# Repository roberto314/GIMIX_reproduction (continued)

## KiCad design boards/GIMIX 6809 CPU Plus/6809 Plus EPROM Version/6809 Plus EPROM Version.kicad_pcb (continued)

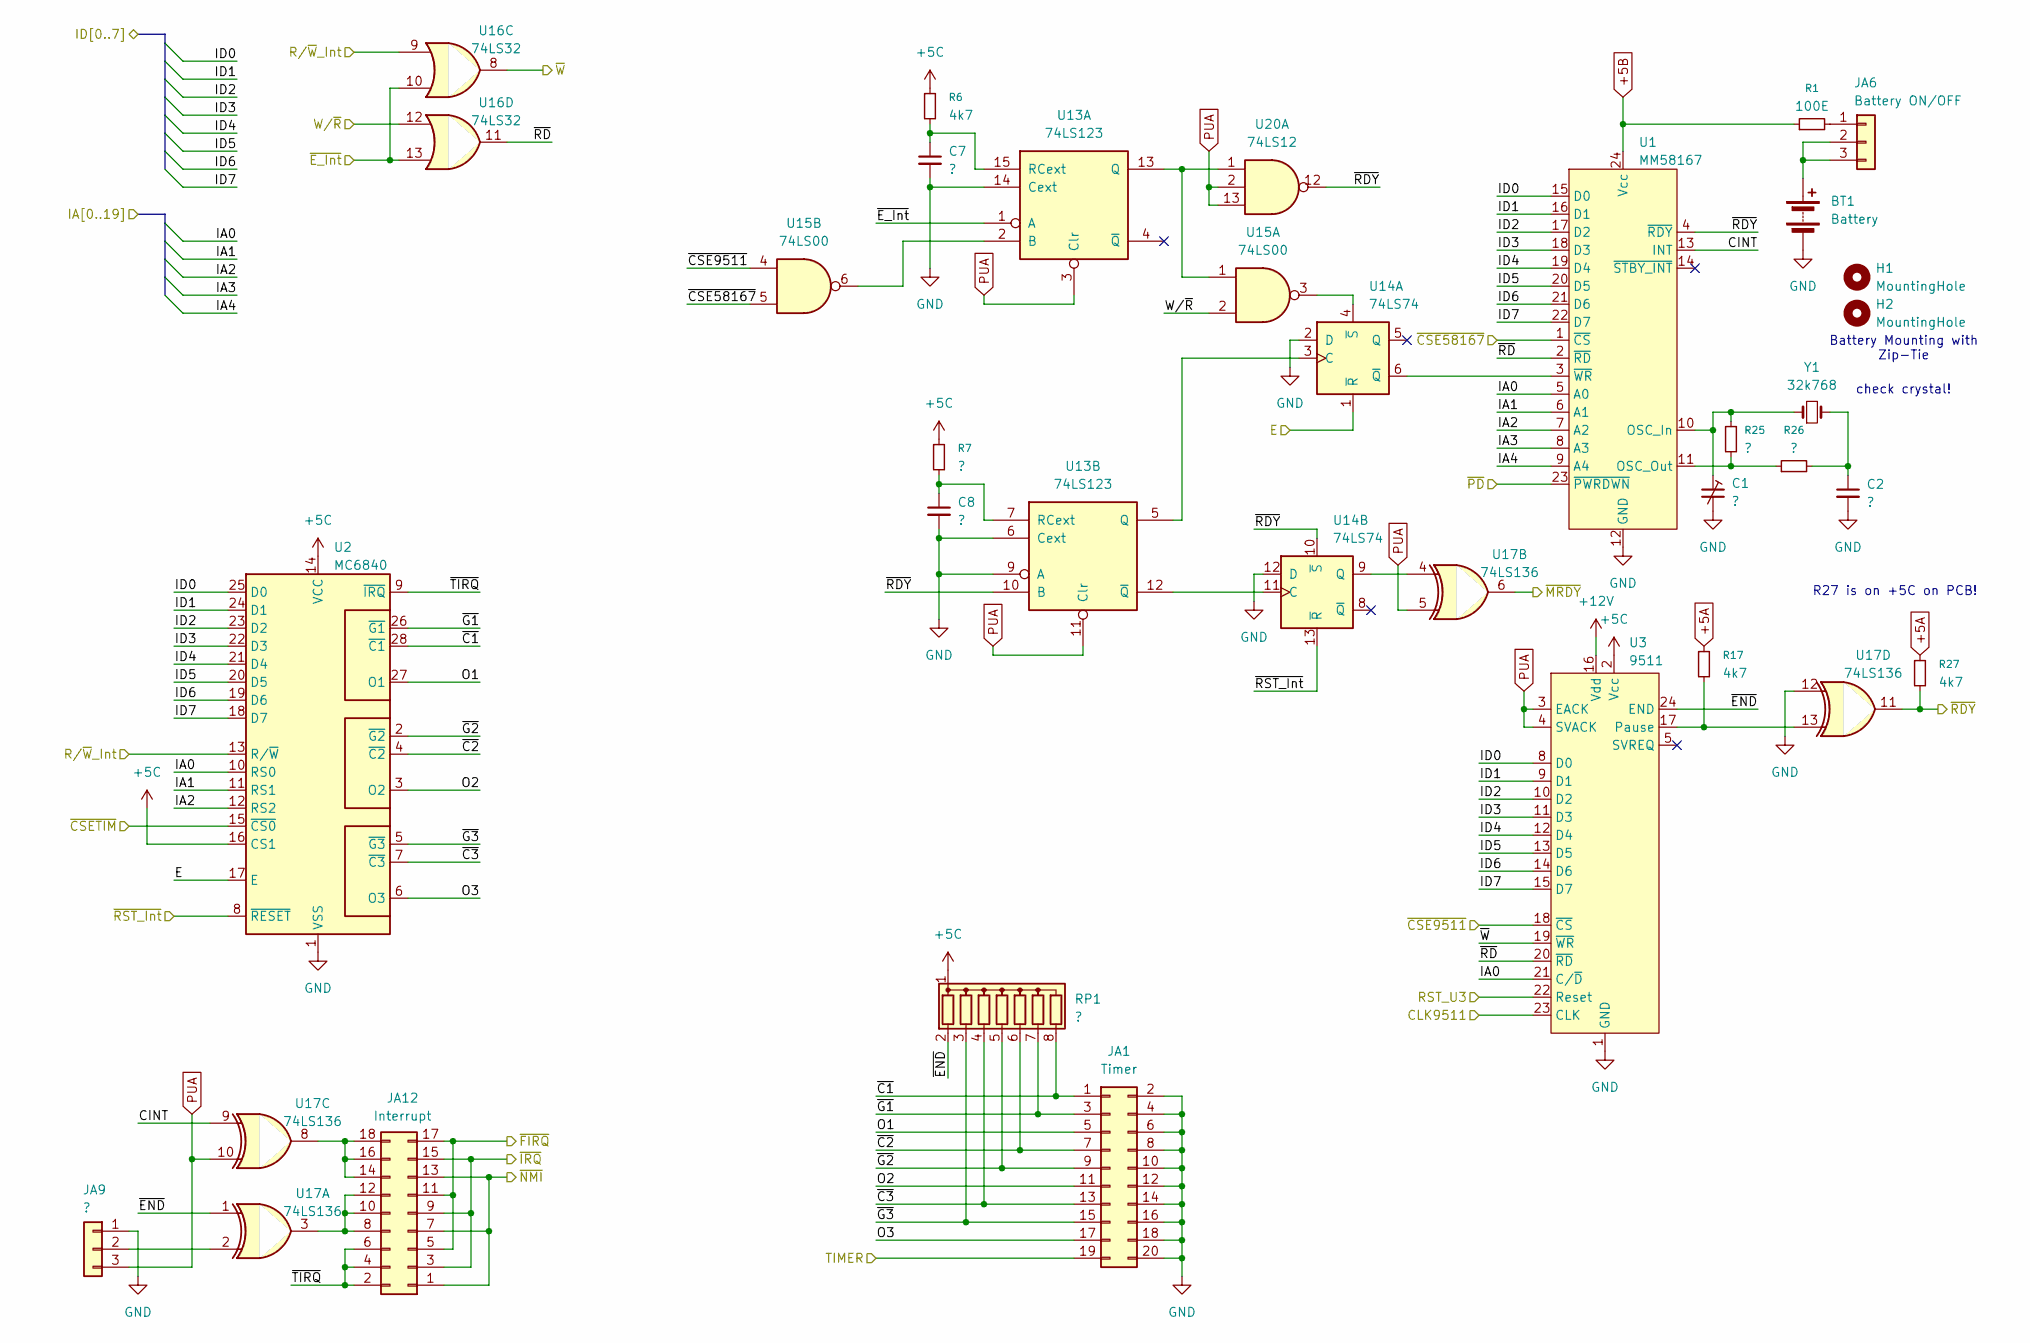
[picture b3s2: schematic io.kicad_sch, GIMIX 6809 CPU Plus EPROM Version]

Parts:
BT1: Battery; Varta_3V200HSKSPCBD
C1: ?; C_Trim_3pin
C2, C7, C8: ?; C_Disc_D6.0mm_W2.5mm_P5.00mm
H1, H2: MountingHole; MountingHole_2.7mm
JA1: Timer; PinHeader_2x10_P2.54mm_Vertical
JA6: Battery ON/OFF; PinHeader_1x03_P2.54mm_Vertical
JA9: ?; PinHeader_1x03_P2.54mm_Vertical
JA12: Interrupt; PinHeader_2x09_P2.54mm_Vertical
R1: 100E; R_Axial_DIN0207_L6.3mm_D2.5mm_P10.16mm_Horizontal
R6, R17, R27: 4k7; R_Axial_DIN0207_L6.3mm_D2.5mm_P10.16mm_Horizontal
R7, R25, R26: ?; R_Axial_DIN0207_L6.3mm_D2.5mm_P10.16mm_Horizontal
RP1: ?; R_Array_SIP8
U1: MM58167; DIP-24_W15.24mm
U2: MC6840; DIP-28_W15.24mm
U3: 9511; DIP-24_W15.24mm
U13: 74LS123; DIP-16_W7.62mm
U14: 74LS74; DIP-14_W7.62mm
U15: 74LS00; DIP-14_W7.62mm
U16: 74LS32; DIP-14_W7.62mm
U17: 74LS136; DIP-14_W7.62mm
U20: 74LS12; DIP-14_W7.62mm
Y1: 32k768; Crystal_AT310_D3.0mm_L10.0mm_Horizontal

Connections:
+5A: R17.1, R27.1; also elsewhere on the board
+5B: R1.1, U1.24 (Vcc); also elsewhere on the board
+5C: R6.1, R7.1, RP1.1 (common), U2.14 (VCC), U2.16 (CS1), U3.2 (Vcc); also elsewhere on the board
+12V: U3.16 (Vdd); also elsewhere on the board
/Clock/CLK9511: U3.23 (CLK); also elsewhere on the board
/Clock/TIMER: JA1.19; also elsewhere on the board
/E: U2.17 (E), U14.1 (~R); also elsewhere on the board
/IA0: U1.5 (A0), U2.10 (RS0), U3.21 (C/~D); also elsewhere on the board
/IA1: U1.6 (A1), U2.11 (RS1); also elsewhere on the board
/IA2: U1.7 (A2), U2.12 (RS2); also elsewhere on the board
/IA3: U1.8 (A3); also elsewhere on the board
/IA4: U1.9 (A4); also elsewhere on the board
/ID0: U1.15 (D0), U2.25 (D0), U3.8 (D0); also elsewhere on the board
/ID1: U1.16 (D1), U2.24 (D1), U3.9 (D1); also elsewhere on the board
/ID2: U1.17 (D2), U2.23 (D2), U3.10 (D2); also elsewhere on the board
/ID3: U1.18 (D3), U2.22 (D3), U3.11 (D3); also elsewhere on the board
/ID4: U1.19 (D4), U2.21 (D4), U3.12 (D4); also elsewhere on the board
/ID5: U1.20 (D5), U2.20 (D5), U3.13 (D5); also elsewhere on the board
/ID6: U1.21 (D6), U2.19 (D6), U3.14 (D6); also elsewhere on the board
/ID7: U1.22 (D7), U2.18 (D7), U3.15 (D7); also elsewhere on the board
/IO/CINT: U1.13 (INT), U17.9
/IO/O1: JA1.5, U2.27 (O1)
/IO/O2: JA1.11, U2.3 (O2)
/IO/O3: JA1.17, U2.6 (O3)
/IO/~C1: JA1.1, RP1.8 (R7), U2.28 (~C1)
/IO/~C2: JA1.7, RP1.6 (R5), U2.4 (~C2)
/IO/~C3: JA1.13, RP1.4 (R3), U2.7 (~C3)
/IO/~END: RP1.2 (R1), U3.24 (END), U17.1
/IO/~G1: JA1.3, RP1.7 (R6), U2.26 (~G1)
/IO/~G2: JA1.9, RP1.5 (R4), U2.2 (~G2)
/IO/~G3: JA1.15, RP1.3 (R2), U2.5 (~G3)
/IO/~RD: U1.2 (~RD), U3.20 (~RD), U16.11
/IO/~TIRQ: JA12.2, JA12.4, JA12.6, U2.9 (~IRQ)
/RST_U3: U3.22 (Reset); also elsewhere on the board
/R/~W_Int: U2.13 (R/~W), U16.9; also elsewhere on the board
/W/~R: U15.2, U16.12; also elsewhere on the board
/~CSE9511: U3.18 (~CS), U15.4; also elsewhere on the board
/~CSE58167: U1.1 (~CS), U15.5; also elsewhere on the board
/~CSETIM: U2.15 (~CS0); also elsewhere on the board
/~E_Int: U13.1 (A), U16.10, U16.13; also elsewhere on the board
/~FIRQ: JA12.5, JA12.11, JA12.17; also elsewhere on the board
/~IRQ: JA12.3, JA12.9, JA12.15; also elsewhere on the board
/~MRDY: U17.6; also elsewhere on the board
/~NMI: JA12.1, JA12.7, JA12.13; also elsewhere on the board
/~PD: U1.23 (~PWRDWN); also elsewhere on the board
/~RDY: R27.2, U1.4 (~RDY), U13.10 (B), U14.10 (~S), U17.11, U20.12
/~RST_Int: U2.8 (~RESET), U14.13 (~R); also elsewhere on the board
/~W: U3.19 (~WR), U16.8; also elsewhere on the board
GND: BT1.2 (-), C1.2, C2.2, C7.2, C8.2, JA1.2, JA1.4, JA1.6, JA1.8, JA1.10, JA1.12, JA1.14, JA1.16, JA1.18, JA1.20, JA9.1, U1.12 (GND), U2.1 (VSS), U3.1 (GND), U13.6 (Cext), U13.9 (A), U13.14 (Cext), U14.2 (D), U14.12 (D), U17.12; also elsewhere on the board
unnamed: BT1.1 (+), JA6.2, JA6.3
unnamed: C2.1, R26.2, Y1.2
unnamed: JA6.1, R1.2
unnamed: JA9.2, U17.2
unnamed: JA12.8, JA12.10, JA12.12, U17.3
unnamed: JA12.14, JA12.16, JA12.18, U17.8
unnamed: C1.1, R25.1, U1.10 (OSC_In), Y1.1
unnamed: R25.2, R26.1, U1.11 (OSC_Out)
unnamed: U1.3 (~WR), U14.6 (~Q)
unnamed: R17.2, U3.17 (Pause), U17.13
unnamed: U13.2 (B), U15.6
unnamed: U13.13 (Q), U15.1, U20.1
unnamed: C7.1, R6.2, U13.15 (RCext)
unnamed: U13.5 (Q), U14.3 (C)
unnamed: C8.1, R7.2, U13.7 (RCext)
unnamed: U13.12 (~Q), U14.11 (C)
unnamed: U14.4 (~S), U15.3
unnamed: U14.9 (Q), U17.4
PUA: JA9.3, U3.3 (EACK), U3.4 (SVACK), U13.3 (Clr), U13.11 (Clr), U17.5, U17.10, U20.2, U20.13; also elsewhere on the board

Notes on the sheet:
Battery Mounting with Zip-Tie
check crystal!
R27 is on +5C on PCB!

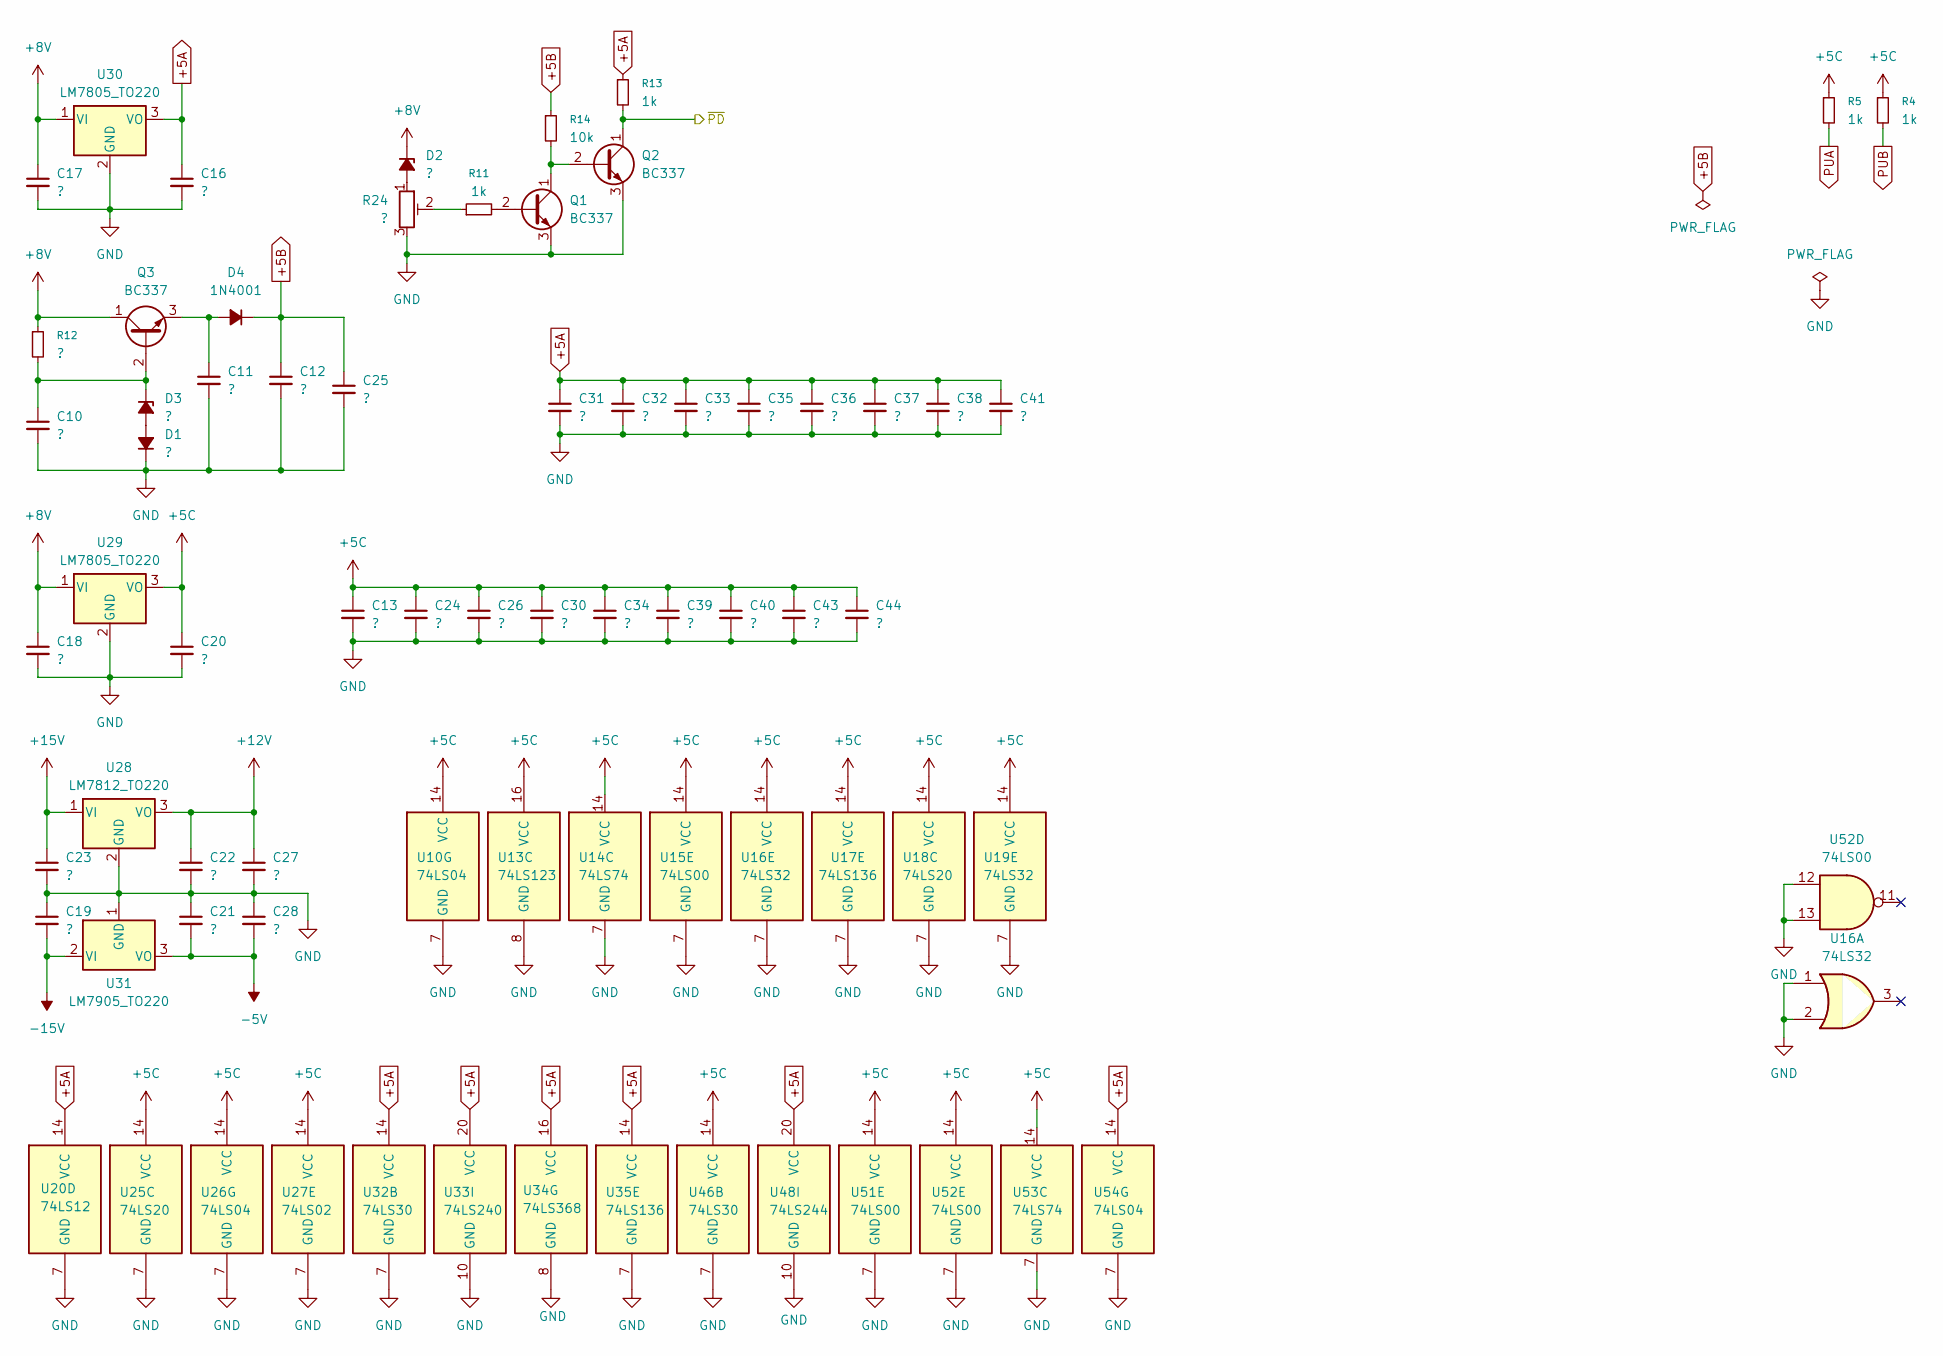
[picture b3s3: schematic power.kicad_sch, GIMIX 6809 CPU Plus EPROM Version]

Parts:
C10, C11, C12, C13, C16, C17, C18, C19, C20, C21, C22, C23, C24, C25, C26, C27, C28, C30, C31, C32, C33, C34, C35, C36, C37, C38, C39, C40, C41, C43, C44: ?; C_Disc_D3.8mm_W2.6mm_P2.50mm
D1, D2, D3: ?; D_DO-34_SOD68_P10.16mm_Horizontal
D4: 1N4001; D_DO-34_SOD68_P10.16mm_Horizontal
Q1, Q2, Q3: BC337; TO-92_Inline
R4, R5, R11, R13: 1k; R_Axial_DIN0207_L6.3mm_D2.5mm_P10.16mm_Horizontal
R12: ?; R_Axial_DIN0207_L6.3mm_D2.5mm_P10.16mm_Horizontal
R14: 10k; R_Axial_DIN0207_L6.3mm_D2.5mm_P10.16mm_Horizontal
R24: ?; Potentiometer_Bourns_3339P_Vertical
U10, U26, U54: 74LS04; DIP-14_W7.62mm
U13: 74LS123; DIP-16_W7.62mm
U14, U53: 74LS74; DIP-14_W7.62mm
U15, U51, U52: 74LS00; DIP-14_W7.62mm
U16, U19: 74LS32; DIP-14_W7.62mm
U17, U35: 74LS136; DIP-14_W7.62mm
U18, U25: 74LS20; DIP-14_W7.62mm
U20: 74LS12; DIP-14_W7.62mm
U27: 74LS02; DIP-14_W7.62mm
U28: LM7812_TO220; TO-220-3_Horizontal_TabDown
U29, U30: LM7805_TO220; TO-220-3_Horizontal_TabDown
U31: LM7905_TO220; TO-220-3_Horizontal_TabDown
U32, U46: 74LS30; DIP-14_W7.62mm
U33: 74LS240; DIP-20_W7.62mm
U34: 74LS368; DIP-16_W7.62mm
U48: 74LS244; DIP-20_W7.62mm

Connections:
+5A: C16.1, C31.1, C32.1, C33.1, C35.1, C36.1, C37.1, C38.1, C41.1, R13.1, U20.14 (VCC), U30.3 (VO), U32.14 (VCC), U33.20 (VCC), U34.16 (VCC), U35.14 (VCC), U48.20 (VCC), U54.14 (VCC); also elsewhere on the board
+5B: C12.1, C25.1, D4.1 (K), R14.1; also elsewhere on the board
+5C: C13.1, C20.1, C24.1, C26.1, C30.1, C34.1, C39.1, C40.1, C43.1, C44.1, R4.1, R5.1, U10.14 (VCC), U13.16 (VCC), U14.14 (VCC), U15.14 (VCC), U16.14 (VCC), U17.14 (VCC), U18.14 (VCC), U19.14 (VCC), U25.14 (VCC), U26.14 (VCC), U27.14 (VCC), U29.3 (VO), U46.14 (VCC), U51.14 (VCC), U52.14 (VCC), U53.14 (VCC); also elsewhere on the board
+8V: C17.1, C18.1, D2.1 (K), Q3.1 (C), R12.1, U29.1 (VI), U30.1 (VI); also elsewhere on the board
+12V: C22.1, C27.1, U28.3 (VO); also elsewhere on the board
+15V: C23.1, U28.1 (VI); also elsewhere on the board
-5V: C21.2, C28.2, U31.3 (VO); also elsewhere on the board
-15V: C19.2, U31.2 (VI); also elsewhere on the board
/~PD: Q2.1 (C), R13.2; also elsewhere on the board
GND: C10.2, C11.2, C12.2, C13.2, C16.2, C17.2, C18.2, C19.1, C20.2, C21.1, C22.2, C23.2, C24.2, C25.2, C26.2, C27.2, C28.1, C30.2, C31.2, C32.2, C33.2, C34.2, C35.2, C36.2, C37.2, C38.2, C39.2, C40.2, C41.2, C43.2, C44.2, D1.1 (K), Q1.3 (E), Q2.3 (E), R24.3, U10.7 (GND), U13.8 (GND), U14.7 (GND), U15.7 (GND), U16.1, U16.2, U16.7 (GND), U17.7 (GND), U18.7 (GND), U19.7 (GND), U20.7 (GND), U25.7 (GND), U26.7 (GND), U27.7 (GND), U28.2 (GND), U29.2 (GND), U30.2 (GND), U31.1 (GND), U32.7 (GND), U33.10 (GND), U34.8 (GND), U35.7 (GND), U46.7 (GND), U48.10 (GND), U51.7 (GND), U52.7 (GND), U52.12, U52.13, U53.7 (GND), U54.7 (GND); also elsewhere on the board
unnamed: D1.2 (A), D3.2 (A)
unnamed: D2.2 (A), R24.1
unnamed: C10.1, D3.1 (K), Q3.2 (B), R12.2
unnamed: C11.1, D4.2 (A), Q3.3 (E)
unnamed: Q1.2 (B), R11.2
unnamed: Q1.1 (C), Q2.2 (B), R14.2
unnamed: R11.1, R24.2
PUA: R5.2; also elsewhere on the board
PUB: R4.2; also elsewhere on the board

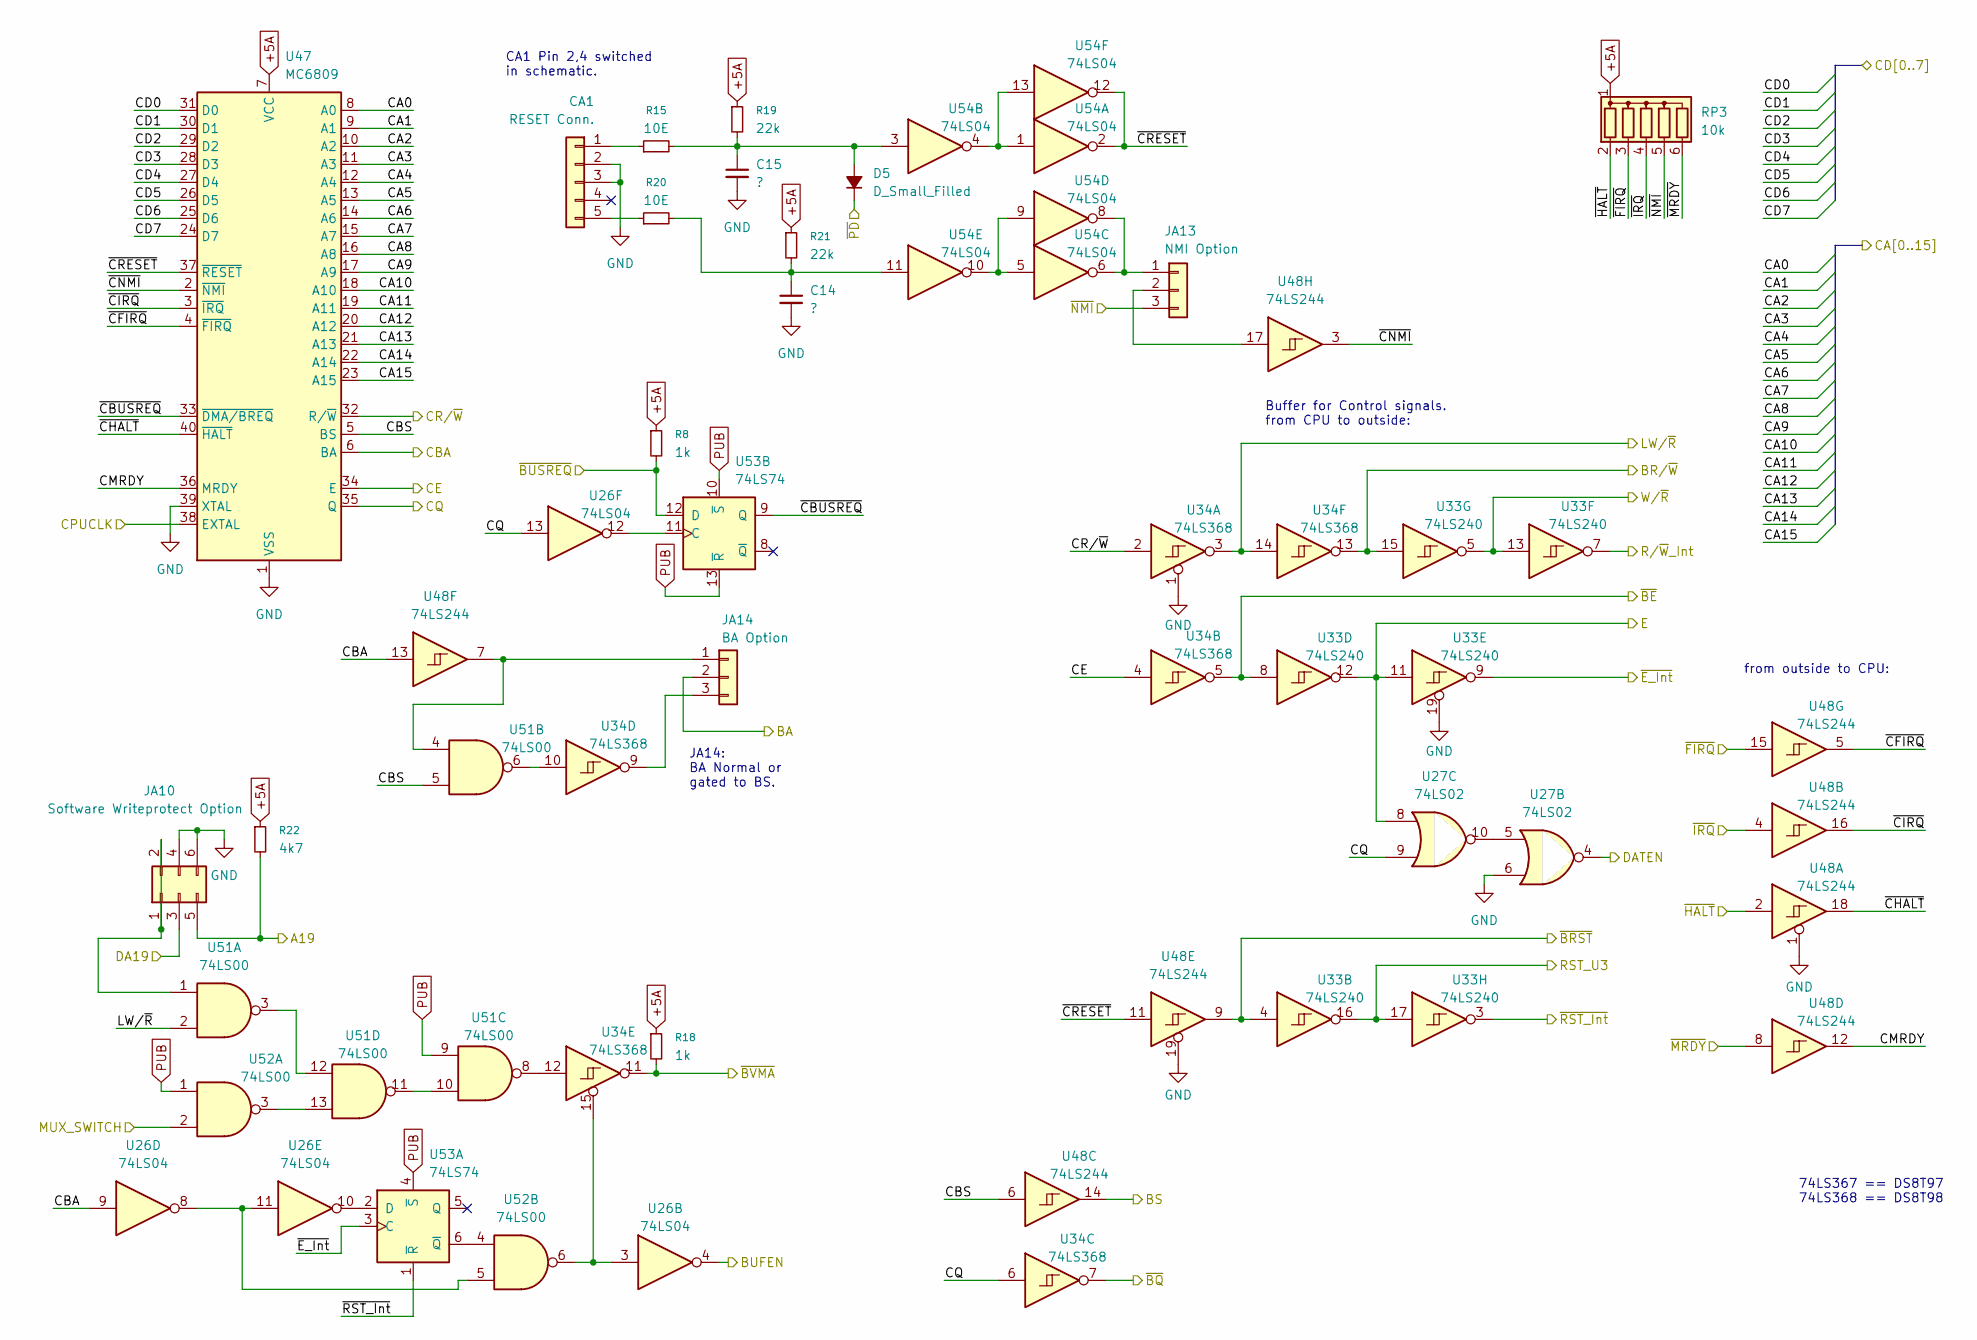
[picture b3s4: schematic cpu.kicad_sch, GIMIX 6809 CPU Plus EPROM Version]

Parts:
C14, C15: ?; C_Disc_D3.8mm_W2.6mm_P2.50mm
CA1: RESET Conn.; PinHeader_1x05_P2.54mm_Vertical
D5: D_Small_Filled; D_DO-34_SOD68_P10.16mm_Horizontal
JA10: Software Writeprotect Option; PinHeader_2x03_P2.54mm_Vertical
JA13: NMI Option; PinHeader_1x03_P2.54mm_Vertical
JA14: BA Option; PinHeader_1x03_P2.54mm_Vertical
R8, R18: 1k; R_Axial_DIN0207_L6.3mm_D2.5mm_P10.16mm_Horizontal
R15, R20: 10E; R_Axial_DIN0207_L6.3mm_D2.5mm_P10.16mm_Horizontal
R19, R21: 22k; R_Axial_DIN0207_L6.3mm_D2.5mm_P10.16mm_Horizontal
R22: 4k7; R_Axial_DIN0207_L6.3mm_D2.5mm_P10.16mm_Horizontal
RP3: 10k; R_Array_SIP6
U26, U54: 74LS04; DIP-14_W7.62mm
U27: 74LS02; DIP-14_W7.62mm
U33: 74LS240; DIP-20_W7.62mm
U34: 74LS368; DIP-16_W7.62mm
U47: MC6809; DIP-40_W15.24mm
U48: 74LS244; DIP-20_W7.62mm
U51, U52: 74LS00; DIP-14_W7.62mm
U53: 74LS74; DIP-14_W7.62mm

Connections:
+5A: R8.1, R18.1, R19.1, R21.1, R22.1, RP3.1 (common), U47.7 (VCC); also elsewhere on the board
/A19: JA10.5, R22.2; also elsewhere on the board
/BA: JA14.2; also elsewhere on the board
/BR/~W: U33.15, U34.13; also elsewhere on the board
/BS: U48.14; also elsewhere on the board
/BUFEN: U26.4; also elsewhere on the board
/CA0: U47.8 (A0); also elsewhere on the board
/CA1: U47.9 (A1); also elsewhere on the board
/CA2: U47.10 (A2); also elsewhere on the board
/CA3: U47.11 (A3); also elsewhere on the board
/CA4: U47.12 (A4); also elsewhere on the board
/CA5: U47.13 (A5); also elsewhere on the board
/CA6: U47.14 (A6); also elsewhere on the board
/CA7: U47.15 (A7); also elsewhere on the board
/CA8: U47.16 (A8); also elsewhere on the board
/CA9: U47.17 (A9); also elsewhere on the board
/CA10: U47.18 (A10); also elsewhere on the board
/CA11: U47.19 (A11); also elsewhere on the board
/CA12: U47.20 (A12); also elsewhere on the board
/CA13: U47.21 (A13); also elsewhere on the board
/CA14: U47.22 (A14); also elsewhere on the board
/CA15: U47.23 (A15); also elsewhere on the board
/CBA: U26.9, U47.6 (BA), U48.13
/CD0: U47.31 (D0); also elsewhere on the board
/CD1: U47.30 (D1); also elsewhere on the board
/CD2: U47.29 (D2); also elsewhere on the board
/CD3: U47.28 (D3); also elsewhere on the board
/CD4: U47.27 (D4); also elsewhere on the board
/CD5: U47.26 (D5); also elsewhere on the board
/CD6: U47.25 (D6); also elsewhere on the board
/CD7: U47.24 (D7); also elsewhere on the board
/CE: U34.4, U47.34 (E); also elsewhere on the board
/CPU/CBS: U47.5 (BS), U48.6, U51.5
/CPU/CMRDY: U47.36 (MRDY), U48.12
/CPU/CPUCLK: U47.38 (EXTAL); also elsewhere on the board
/CPU/~CBUSREQ: U47.33 (~DMA/BREQ), U53.9 (Q)
/CPU/~CFIRQ: U47.4 (~FIRQ), U48.5
/CPU/~CHALT: U47.40 (~HALT), U48.18
/CPU/~CIRQ: U47.3 (~IRQ), U48.16
/CPU/~CNMI: U47.2 (~NMI), U48.3
/CPU/~CRESET: U47.37 (~RESET), U48.11, U54.2, U54.12
/CQ: U26.13, U27.9, U34.6, U47.35 (Q)
/CR/~W: U34.2, U47.32 (R/~W); also elsewhere on the board
/DA19: JA10.3; also elsewhere on the board
/DATEN: U27.4; also elsewhere on the board
/E: U27.8, U33.11, U33.12; also elsewhere on the board
/LW/~R: U34.3, U34.14, U51.2; also elsewhere on the board
/MUX_SWITCH: U52.2; also elsewhere on the board
/RST_U3: U33.16, U33.17; also elsewhere on the board
/R/~W_Int: U33.7; also elsewhere on the board
/W/~R: U33.5, U33.13; also elsewhere on the board
/~BE: U33.8, U34.5; also elsewhere on the board
/~BQ: U34.7; also elsewhere on the board
/~BRST: U33.4, U48.9; also elsewhere on the board
/~BUSREQ: R8.2, U53.12 (D); also elsewhere on the board
/~BVMA: R18.2, U34.11; also elsewhere on the board
/~E_Int: U33.9, U53.3 (C); also elsewhere on the board
/~FIRQ: RP3.3 (R2), U48.15; also elsewhere on the board
/~HALT: RP3.2 (R1), U48.2; also elsewhere on the board
/~IRQ: RP3.4 (R3), U48.4; also elsewhere on the board
/~MRDY: RP3.6 (R5), U48.8; also elsewhere on the board
/~NMI: JA13.3, RP3.5 (R4); also elsewhere on the board
/~PD: D5.1 (K); also elsewhere on the board
/~RST_Int: U33.3, U53.1 (~R); also elsewhere on the board
GND: C14.2, C15.2, CA1.2, CA1.3, JA10.4, JA10.6, U27.6, U33.19, U34.1, U47.1 (VSS), U47.39 (XTAL), U48.1, U48.19; also elsewhere on the board
unnamed: C14.1, R20.2, R21.2, U54.11
unnamed: CA1.1, R15.1
unnamed: CA1.5, R20.1
unnamed: C15.1, D5.2 (A), R15.2, R19.2, U54.3
unnamed: JA10.1, JA10.2, U51.1
unnamed: JA13.1, U54.6, U54.8
unnamed: JA13.2, U48.17
unnamed: JA14.1, U48.7, U51.4
unnamed: JA14.3, U34.9
unnamed: U26.3, U34.15, U52.6
unnamed: U26.8, U26.11, U52.5
unnamed: U27.5, U27.10
unnamed: U34.10, U51.6
unnamed: U34.12, U51.8
unnamed: U51.10, U51.11
unnamed: U51.3, U51.12
unnamed: U51.13, U52.3
unnamed: U26.10, U53.2 (D)
unnamed: U52.4, U53.6 (~Q)
unnamed: U26.12, U53.11 (C)
unnamed: U54.1, U54.4, U54.13
unnamed: U54.5, U54.9, U54.10
PUB: U51.9, U52.1, U53.4 (~S), U53.10 (~S), U53.13 (~R); also elsewhere on the board

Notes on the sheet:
74LS367 == DS8T97 74LS368 == DS8T98
CA1 Pin 2,4 switched in schematic.
Buffer for Control signals. from CPU to outside:
from outside to CPU:
JA14: BA Normal or gated to BS.

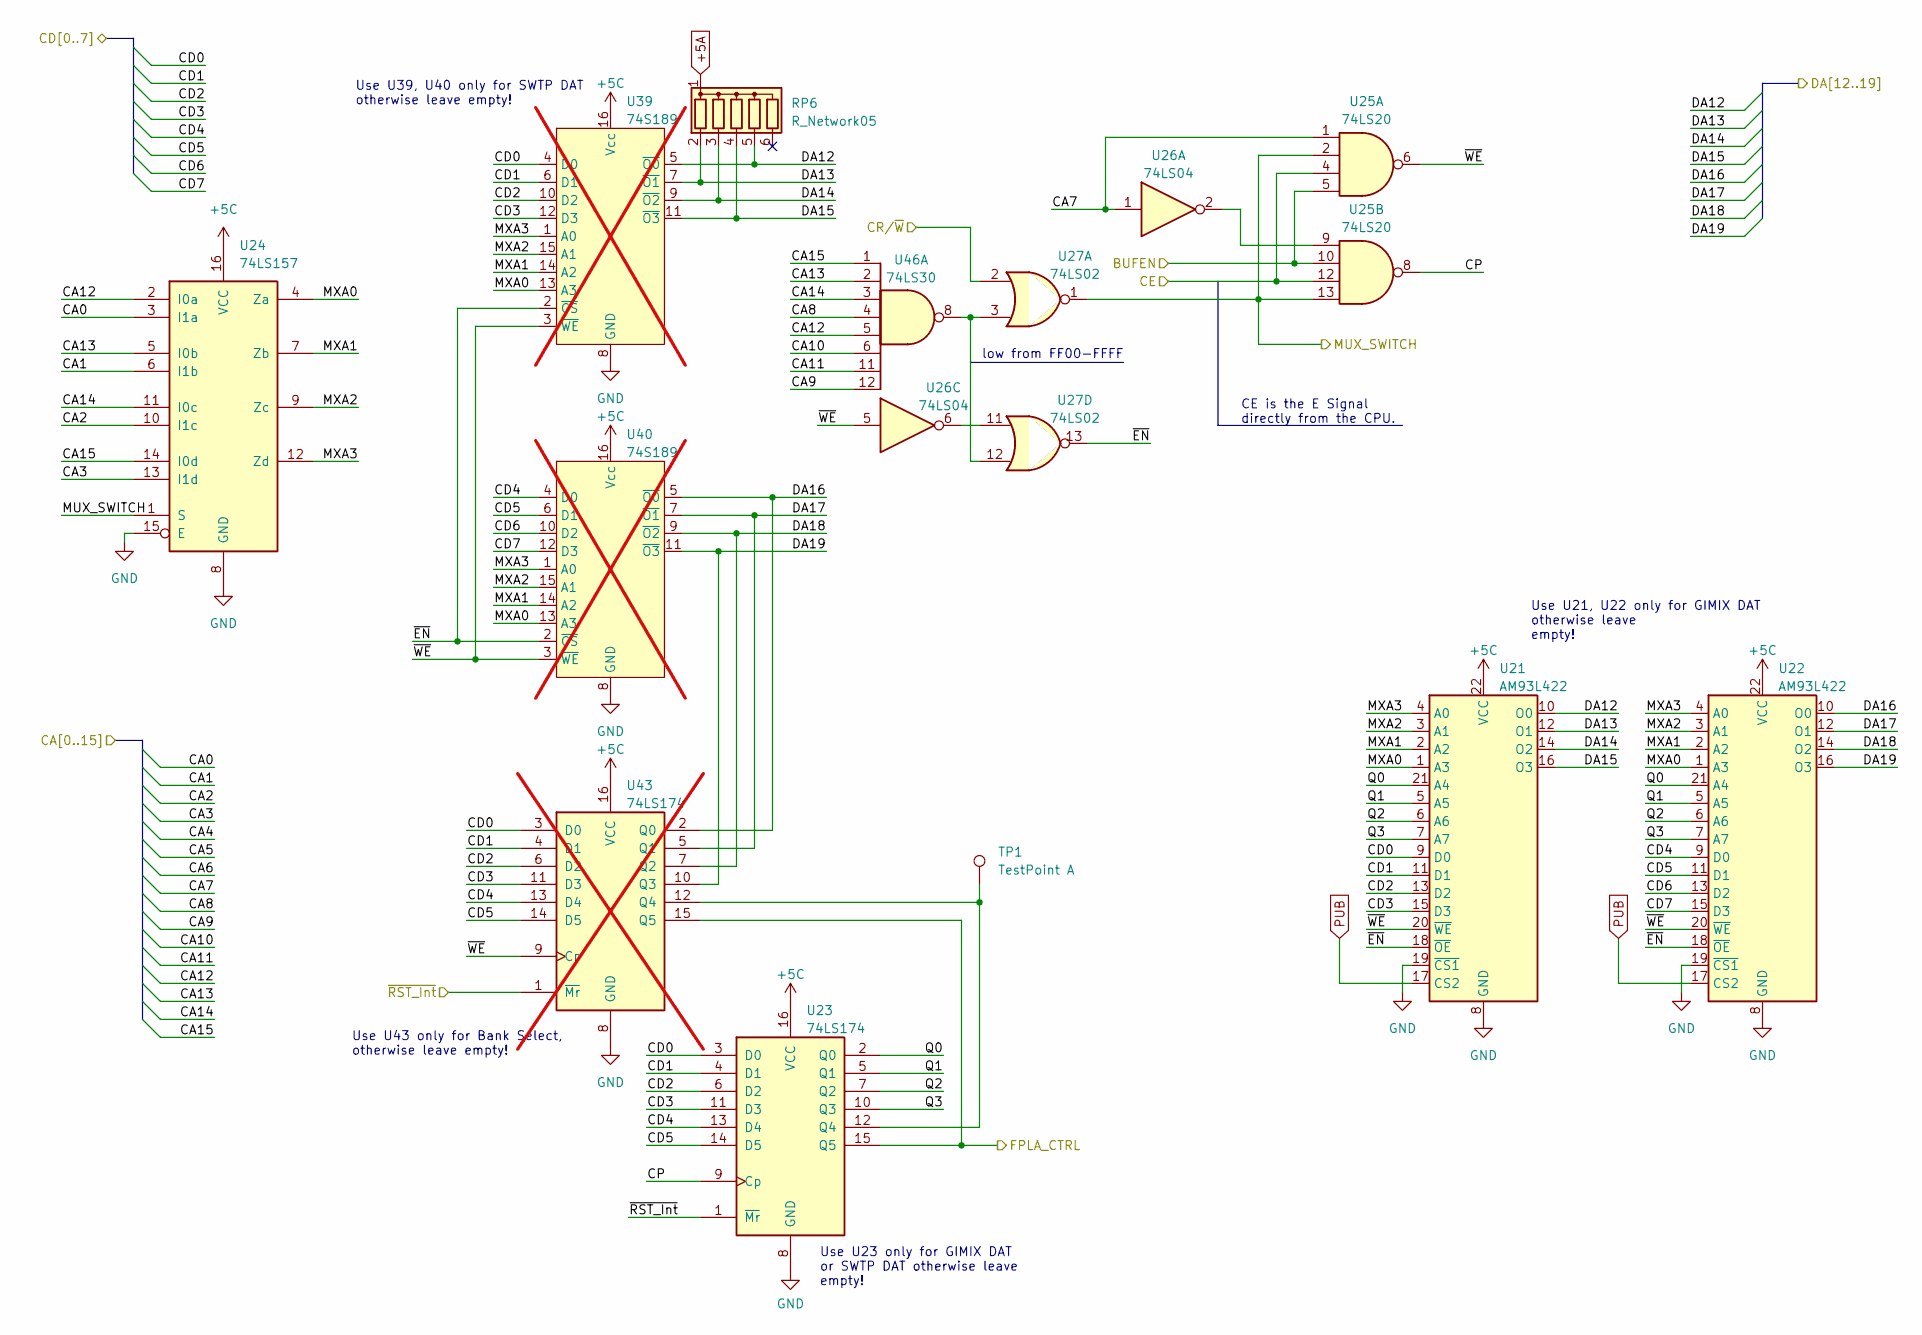
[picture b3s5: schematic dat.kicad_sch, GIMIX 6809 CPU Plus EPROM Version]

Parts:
RP6: R_Network05; R_Array_SIP6
TP1: TestPoint A; PinHeader_1x01_P2.54mm_Vertical
U21, U22: AM93L422; DIP-22_W10.16mm
U23: 74LS174; DIP-16_W7.62mm
U24: 74LS157; DIP-16_W7.62mm
U25: 74LS20; DIP-14_W7.62mm
U26: 74LS04; DIP-14_W7.62mm
U27: 74LS02; DIP-14_W7.62mm
U39, U40: 74S189; DIP-16_W7.62mm; not fitted
U43: 74LS174; DIP-16_W7.62mm; not fitted
U46: 74LS30; DIP-14_W7.62mm

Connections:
+5A: RP6.1 (common); also elsewhere on the board
+5C: U21.22 (VCC), U22.22 (VCC), U23.16 (VCC), U24.16 (VCC), U39.16 (Vcc), U40.16 (Vcc), U43.16 (VCC); also elsewhere on the board
/Address Translation/CP: U23.9 (Cp), U25.8
/Address Translation/MXA0: U21.1 (A3), U22.1 (A3), U24.4 (Za), U39.13 (A3), U40.13 (A3)
/Address Translation/MXA1: U21.2 (A2), U22.2 (A2), U24.7 (Zb), U39.14 (A2), U40.14 (A2)
/Address Translation/MXA2: U21.3 (A1), U22.3 (A1), U24.9 (Zc), U39.15 (A1), U40.15 (A1)
/Address Translation/MXA3: U21.4 (A0), U22.4 (A0), U24.12 (Zd), U39.1 (A0), U40.1 (A0)
/Address Translation/Q0: U21.21 (A4), U22.21 (A4), U23.2 (Q0)
/Address Translation/Q1: U21.5 (A5), U22.5 (A5), U23.5 (Q1)
/Address Translation/Q2: U21.6 (A6), U22.6 (A6), U23.7 (Q2)
/Address Translation/Q3: U21.7 (A7), U22.7 (A7), U23.10 (Q3)
/Address Translation/~EN: U21.18 (~OE), U22.18 (~OE), U27.13, U39.2 (~CS), U40.2 (~CS)
/Address Translation/~WE: U21.20 (~WE), U22.20 (~WE), U25.6, U26.5, U39.3 (~WE), U40.3 (~WE), U43.9 (Cp)
/BUFEN: U25.5, U25.10; also elsewhere on the board
/CA0: U24.3 (I1a); also elsewhere on the board
/CA1: U24.6 (I1b); also elsewhere on the board
/CA2: U24.10 (I1c); also elsewhere on the board
/CA3: U24.13 (I1d); also elsewhere on the board
/CA7: U25.1, U26.1; also elsewhere on the board
/CA8: U46.4; also elsewhere on the board
/CA9: U46.12; also elsewhere on the board
/CA10: U46.6; also elsewhere on the board
/CA11: U46.11; also elsewhere on the board
/CA12: U24.2 (I0a), U46.5; also elsewhere on the board
/CA13: U24.5 (I0b), U46.2; also elsewhere on the board
/CA14: U24.11 (I0c), U46.3; also elsewhere on the board
/CA15: U24.14 (I0d), U46.1; also elsewhere on the board
/CD0: U21.9 (D0), U23.3 (D0), U39.4 (D0), U43.3 (D0); also elsewhere on the board
/CD1: U21.11 (D1), U23.4 (D1), U39.6 (D1), U43.4 (D1); also elsewhere on the board
/CD2: U21.13 (D2), U23.6 (D2), U39.10 (D2), U43.6 (D2); also elsewhere on the board
/CD3: U21.15 (D3), U23.11 (D3), U39.12 (D3), U43.11 (D3); also elsewhere on the board
/CD4: U22.9 (D0), U23.13 (D4), U40.4 (D0), U43.13 (D4); also elsewhere on the board
/CD5: U22.11 (D1), U23.14 (D5), U40.6 (D1), U43.14 (D5); also elsewhere on the board
/CD6: U22.13 (D2), U40.10 (D2); also elsewhere on the board
/CD7: U22.15 (D3), U40.12 (D3); also elsewhere on the board
/CE: U25.4, U25.12; also elsewhere on the board
/CR/~W: U27.2; also elsewhere on the board
/DA12: RP6.5 (R4), U21.10 (O0), U39.5 (~O0); also elsewhere on the board
/DA13: RP6.2 (R1), U21.12 (O1), U39.7 (~O1); also elsewhere on the board
/DA14: RP6.3 (R2), U21.14 (O2), U39.9 (~O2); also elsewhere on the board
/DA15: RP6.4 (R3), U21.16 (O3), U39.11 (~O3); also elsewhere on the board
/DA16: U22.10 (O0), U40.5 (~O0), U43.2 (Q0); also elsewhere on the board
/DA17: U22.12 (O1), U40.7 (~O1), U43.5 (Q1); also elsewhere on the board
/DA18: U22.14 (O2), U40.9 (~O2), U43.7 (Q2); also elsewhere on the board
/DA19: U22.16 (O3), U40.11 (~O3), U43.10 (Q3); also elsewhere on the board
/FPLA_CTRL: U23.15 (Q5), U43.15 (Q5); also elsewhere on the board
/MUX_SWITCH: U24.1 (S), U25.2, U25.13, U27.1; also elsewhere on the board
/~RST_Int: U23.1 (~Mr), U43.1 (~Mr); also elsewhere on the board
GND: U21.8 (GND), U21.19 (~CS1), U22.8 (GND), U22.19 (~CS1), U23.8 (GND), U24.8 (GND), U24.15 (E), U39.8 (GND), U40.8 (GND), U43.8 (GND); also elsewhere on the board
unnamed: TP1.1, U23.12 (Q4), U43.12 (Q4)
unnamed: U25.9, U26.2
unnamed: U26.6, U27.11
unnamed: U27.3, U27.12, U46.8
PUB: U21.17 (CS2), U22.17 (CS2); also elsewhere on the board

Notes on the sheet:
Use U39, U40 only for SWTP DAT otherwise leave empty!
low from FF00-FFFF
Use U23 only for GIMIX DAT or SWTP DAT otherwise leave empty!
CE is the E Signal directly from the CPU.
Use U21, U22 only for GIMIX DAT otherwise leave empty!
Use U43 only for Bank Select, otherwise leave empty!

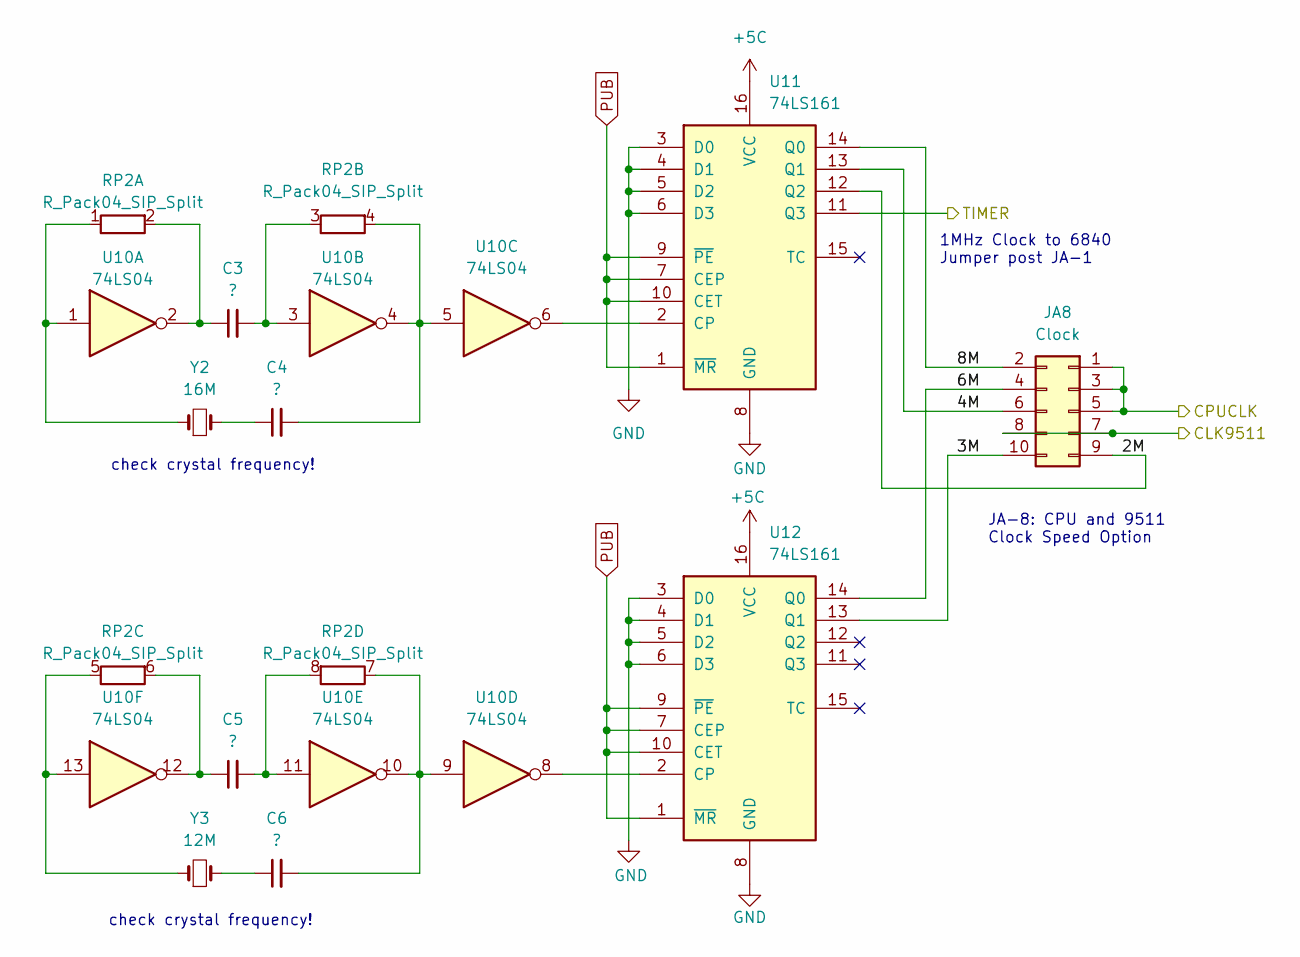
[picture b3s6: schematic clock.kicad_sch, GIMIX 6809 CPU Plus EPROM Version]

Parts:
C3, C4, C5, C6: ?; C_Disc_D6.0mm_W2.5mm_P5.00mm
JA8: Clock; PinHeader_2x05_P2.54mm_Vertical
RP2: R_Pack04_SIP_Split; R_Array_SIP8
U10: 74LS04; DIP-14_W7.62mm
U11, U12: 74LS161; DIP-16_W7.62mm
Y2: 16M; Crystal_HC49-U_Vertical
Y3: 12M; Crystal_HC49-U_Vertical

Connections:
+5C: U11.16 (VCC), U12.16 (VCC); also elsewhere on the board
/CPU/CPUCLK: JA8.1, JA8.3, JA8.5; also elsewhere on the board
/Clock/2M: JA8.9, U11.12 (Q2)
/Clock/3M: JA8.10, U12.13 (Q1)
/Clock/4M: JA8.6, U11.13 (Q1)
/Clock/6M: JA8.4, U12.14 (Q0)
/Clock/8M: JA8.2, U11.14 (Q0)
/Clock/CLK9511: JA8.7, JA8.8; also elsewhere on the board
/Clock/TIMER: U11.11 (Q3); also elsewhere on the board
GND: U11.3 (D0), U11.4 (D1), U11.5 (D2), U11.6 (D3), U11.8 (GND), U12.3 (D0), U12.4 (D1), U12.5 (D2), U12.6 (D3), U12.8 (GND); also elsewhere on the board
unnamed: C4.1, Y2.2
unnamed: C6.1, Y3.2
unnamed: RP2.1 (R1.1), U10.1, Y2.1
unnamed: C3.1, RP2.2 (R1.2), U10.2
unnamed: C3.2, RP2.3 (R2.1), U10.3
unnamed: C4.2, RP2.4 (R2.2), U10.4, U10.5
unnamed: RP2.5 (R3.1), U10.13, Y3.1
unnamed: C5.1, RP2.6 (R3.2), U10.12
unnamed: C6.2, RP2.7 (R4.1), U10.9, U10.10
unnamed: C5.2, RP2.8 (R4.2), U10.11
unnamed: U10.6, U11.2 (CP)
unnamed: U10.8, U12.2 (CP)
PUB: U11.1 (~MR), U11.7 (CEP), U11.9 (~PE), U11.10 (CET), U12.1 (~MR), U12.7 (CEP), U12.9 (~PE), U12.10 (CET); also elsewhere on the board

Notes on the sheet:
JA-8: CPU and 9511 Clock Speed Option
check crystal frequency!
1MHz Clock to 6840 Jumper post JA-1
